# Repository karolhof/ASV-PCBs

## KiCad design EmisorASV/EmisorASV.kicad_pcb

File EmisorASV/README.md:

# Emisor ASV - ESP32 DevKit y LoRa

Esquema con cables continuos y PCB de una cara. El ESP32 se conecta al LoRa por SPI y control; no hay conexiones UART a STM32. Alimentación por USB del DevKit desde el celular en modo host OTG.

## Archivos

- `EmisorASV.kicad_pro`: proyecto KiCad 10.
- `EmisorASV.kicad_sch`: esquema conectado.
- `EmisorASV.kicad_pcb`: PCB principal, cobre solo B.Cu.
- `EmisorASV_Vista_puentes.kicad_pcb`: copia para mostrar alambres en F.Cu; no fabricar esa cara.
- `documentacion/EmisorASV.pdf`: esquema.
- `documentacion/PCB_Emisor_montaje.pdf`: guía de montaje.
- `documentacion/PCB_Impresion_1a1.pdf`: cobre y puentes a escala real, con agujeros.
- `documentacion/Lista_de_materiales.md`: materiales y dimensiones.
- `documentacion/ERC.rpt`, `DRC.json`, `verificar_diseno.py`: verificaciones.
- `fabricacion/Gerber/`: fabricación de una cara; no contiene F.Cu.

## Alimentación y montaje

Antena actual de resorte: J4 y JP2 sin montar. ANT del módulo es pad 16, separado de GND. La ruta SMA es una reserva que requiere validación RF antes de usar antena externa.

El celular debe tener modo host USB OTG y suministrar corriente suficiente. Compatibilidad y autonomía dependen del teléfono/cable y se comprueban en el prototipo. El diseño no incluye firmware ni aplicación del celular.

## Mapa de conexiones, igual al receptor

| Señal | GPIO ESP32 | Pad LoRa |
|---|---:|---:|
| SCK | 18 | 8 |
| MOSI | 23 | 7 |
| MISO | 19 | 6 |
| NSS | 27 | 9 |
| RESET | 14 | 11 |
| DIO0 | 26 | 10 |
| DIO1 | 25 | 2 |
| DIO2 | 33 | 3 |
| VCC | LORA_3V3 | 5 |
| GND | GND | 1, 12, 15 |
| ANT | RF_433 | 16 |

R1/R2 de 10 kΩ mantienen NSS/RESET en alto al arrancar. Los pads LoRa 4, 13, 14 quedan sin conectar. GPIO restantes del ESP32 quedan libres. La huella del ESP32 es la suministrada; la LoRa corresponde a la ya confirmada por el usuario para el receptor. Se respaldaron los archivos anteriores en `documentacion/Emisor_antes_de_actualizar.zip`.

## Fuentes

- [Espressif DevKitC V4: USB, alimentación y pines](https://docs.espressif.com/projects/esp-dev-kits/en/latest/esp32/esp32-devkitc/user_guide.html).
- ZIP del ESP32 y fotos del módulo aportados por el usuario; huella LoRa confirmada en esta conversación.

Las comprobaciones de software no sustituyen las mediciones de 5 V/3,3 V y el ensayo de transmisión del prototipo. Los scripts de generación sobrescriben colocación y esquema; conservar el diseño final antes de ejecutarlos.

## Revisión del 17/11/2026: alimentación directa de 3V3

**U2, C5 y C6 retirados del esquema y de la PCB.** El pin 3V3 de U3 (pad 1) alimenta LORA_3V3: LoRa y pull-ups. C7 de 100 nF y C8 de 10 µF siguen junto al LoRa con conexiones cortas de alimentación y retorno. C4 permanece junto a 5V del ESP32.

No se modifican los GPIO, borneras ni antena. El emisor sigue alimentándose por USB; el receptor conserva entrada de batería, buck de 5V y JP1. Retirar JP1 antes de USB en el receptor. La capacidad de corriente del regulador del DevKit real debe comprobarse durante transmisión; el hardware todavía no fue ensayado.

Los scripts de ruteo intermedio y reportes de revisiones con regulador están archivados en `referencias/proceso_con_U2/`. El archivo principal `.kicad_pcb` es la PCB vigente.

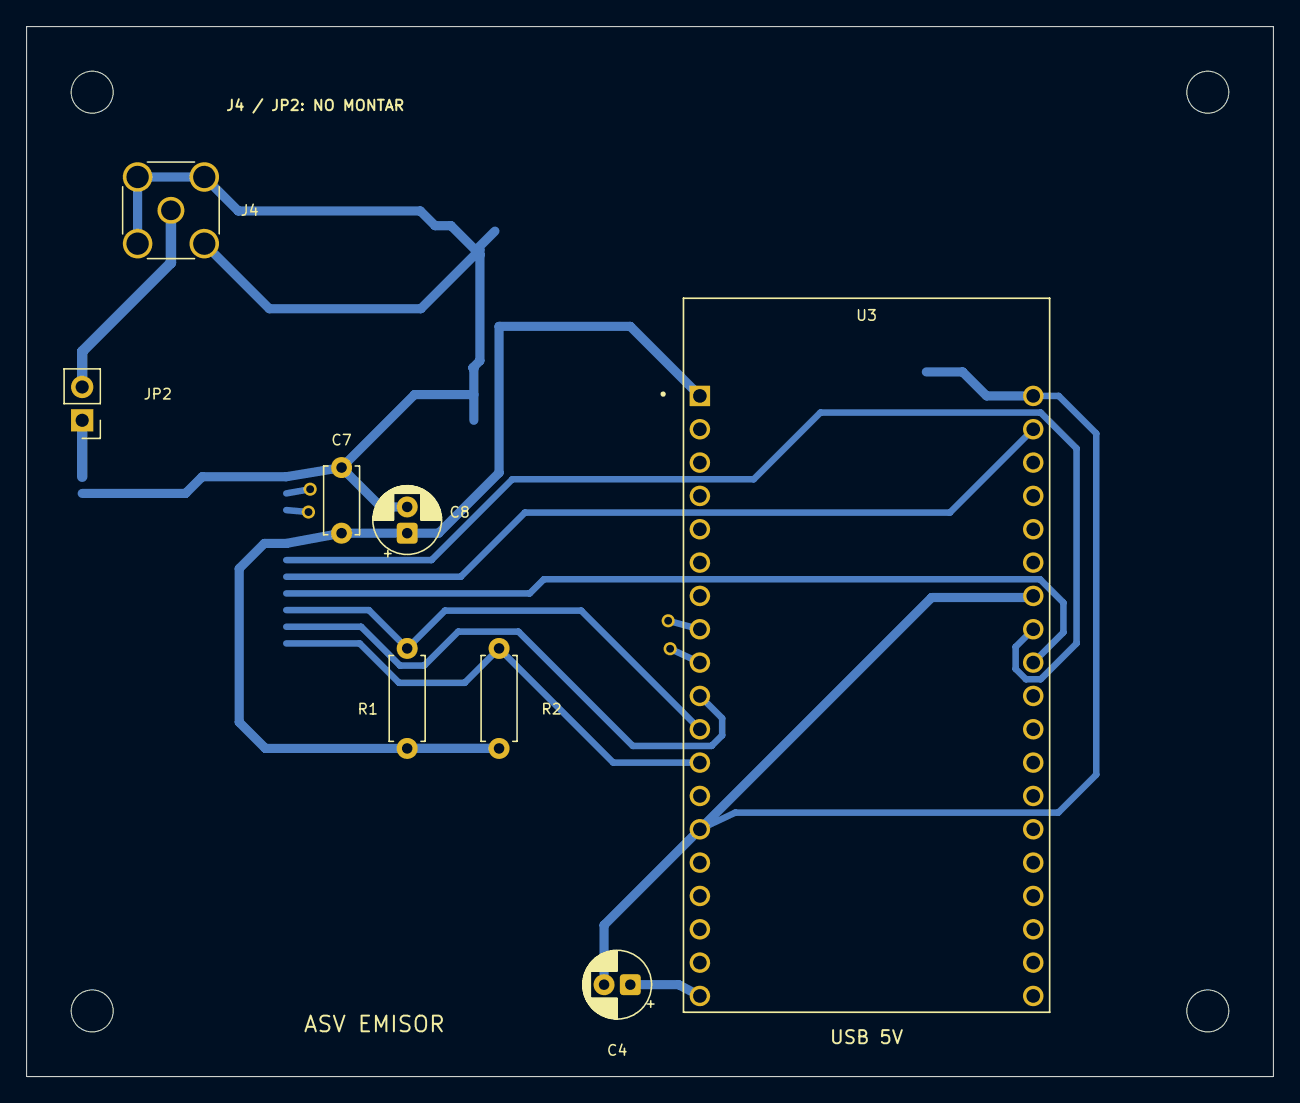
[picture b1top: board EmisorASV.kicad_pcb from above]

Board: 2 copper layers, 95.0 x 80.0 mm, 15 parts (1 on the bottom side), 13 nets.

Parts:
C4: 47u / 25 V; CP_Radial_D5.0mm_P2.00mm
C7: 100n / 50 V; C_Disc_D5.0mm_W2.5mm_P5.00mm
C8: 10u / 25 V; CP_Radial_D5.0mm_P2.00mm
H1, H2, H3, H4: M3; MountingHole_3.2mm_M3
J4: SMA FUTURO - NO MONTAR; SMA_Amphenol_132134_Vertical
JP2: ABIERTO con resorte; PinHeader_1x02_P2.54mm_Vertical
R1, R2: 10k; R_Axial_DIN0207_L6.3mm_D2.5mm_P7.62mm_Horizontal
U3: ESP32-DEVKITC-32UE; ESPRESSIF_ESP32-DEVKITC-32UE
U4: LoRa SX1278 / 433 MHz; XL1278_SMT_16P_16.5x17mm_P1.27mm
W1: ALAMBRE AISLADO; Wire_Jumper_W1_30_00mm
W2: ALAMBRE AISLADO; Wire_Jumper_W2_28_63mm

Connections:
/GND: C4.2, C7.2, C8.2, J4.2, U3.14, U3.20, U3.26, U4.1, U4.12, U4.15
/LORA_3V3: C7.1, C8.1, R1.1, R2.1, U3.1, U4.5
/LORA_DIO0: U3.10, U4.10
/LORA_DIO1: U3.9, U4.2, W1.1
/LORA_DIO2: U3.8, U4.3, W2.1
/LORA_MISO: U3.27, U4.6
/LORA_MOSI: U3.21, U4.7
/LORA_NSS: R1.2, U3.11, U4.9
/LORA_RESET: R2.2, U3.12, U4.11
/LORA_SCK: U3.28, U4.8
/RF_433: JP2.1, U4.16
/RF_SMA: J4.1, JP2.2
/SYS_5V: C4.1, U3.19

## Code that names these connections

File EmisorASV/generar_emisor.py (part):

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route(pp('U3',1),(50.8,pp('U3',1)[1]),(50.8,95.25));mark('U3',1,'LORA_3V3')
for ref,x,key,value,foot in [('C4',292.1,'Device:C_Polarized','47u / 25 V',CAP)]:
 put(key,ref,value,x,63.5,foot=foot)
route(pp('U3',19),(101.6,43.18),(292.1,43.18));mark('U3',19,'SYS_5V');label('SYS_5V',(210.82,43.18))
for ref in ['C4']:tap(ref,1,'SYS_5V',(pp(ref,1)[0],43.18))
route((50.8,95.25),(381,95.25))
tap('U4',5,'LORA_3V3',(269.24,95.25));label('LORA_3V3',(360.68,95.25))
label('GND',(91.44,248.92));route((91.44,248.92),(393.7,248.92));route((393.7,83.82),(393.7,248.92));route((292.1,83.82),(393.7,83.82))
for ref,pin in [('C4',2)]:tap(ref,pin,'GND',(pp(ref,pin)[0],83.82))
for pin in [14,20,26]:tap('U3',pin,'GND',(pp('U3',pin)[0],248.92))
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 if pin not in instances['U3']['nets']:nc('U3',pin)
put('Connector:Conn_Coaxial','J4','SMA FUTURO - NO MONTAR',337.82,129.54,foot='Connector_Coaxial:SMA_Amphenol_132134_Vertical',props=[(337.82,117.475),(337.82,121.285)])
put(rfjump,'JP2','ABIERTO con resorte',311.15,129.54,foot='Connector_PinHeader_2.54mm:PinHeader_1x02_P2.54mm_Vertical',props=[(310,100.33),(310,104.14)])
link('U4',16,'JP2',1,'RF_433');label('RF_433',(299.72,129.54));link('JP2',2,'J4',1,'RF_SMA');label('RF_SMA',(321.31,129.54));tap('J4',2,'GND',(337.82,190.5))
for ref,x,key,value,foot in [('C7',355.6,'Device:C','100n / 50 V',CER),('C8',381,'Device:C_Polarized','10u / 25 V',CAP)]:
 put(key,ref,value,x,160.02,foot=foot);tap(ref,1,'LORA_3V3',(x,95.25));tap(ref,2,'GND',(x,190.5))
for ref,x,y,net in [('#FLG01',137.16,248.92,'GND'),('#FLG02',160.02,43.18,'SYS_5V')]:
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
